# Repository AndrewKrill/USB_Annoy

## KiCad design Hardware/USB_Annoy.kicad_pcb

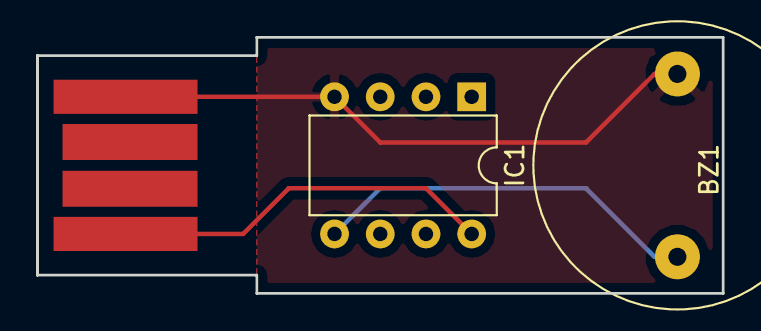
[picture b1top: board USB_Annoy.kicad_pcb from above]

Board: 2 copper layers, 38.1 x 14.2 mm, 3 parts (0 on the bottom side), 3 nets.

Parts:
BZ1: Buzzer; BUZZER
IC1: ATTINY85-P; DIP-8_W7.62mm
J2: USB_A_PLUG; usb-PCB

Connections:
GND: BZ1.1, IC1.4, J2.4
unnamed: BZ1.2, IC1.5
VCC: IC1.8, J2.1

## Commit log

2017-03-09 :confetti_ball: Added .gitattributes & .gitignore files
2017-03-09 Rev 1.0
